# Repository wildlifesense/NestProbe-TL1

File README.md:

# NestProbe TL1

This repository has moved to [https://github.com/NikosVallianos/NestProbe/TL1](https://github.com/NikosVallianos/NestProbe/TL1)

I've used the TL1 reliably for over a year, but have also stared developing the TL2, which uses the Si7051 temperature sensor and the ATtiny816 MCU.
The NestProbe TL1 is a low cost, high accuracy, long-life temperature logger
developed at Wildlife Sense for sea turtle egg incubation research. This repository

Some aspects and decisions during development have been documented at [hackaday.io/project/27560-low-costpowersize-temperature-logger](https://hackaday.io/project/27560-low-costpowersize-temperature-logger).

The main components in the TL1 are:

| Component          | Model       |
|:-------------------|:------------|
| Microcontroller    | ATmega328PB |
| Temperature sensor | MAX30205    |
| EEPROM Memory      | AT25DN512C  |
| Crystal oscillator | ECS-.327-7-34B-C-TR (32.768kHz) |
| Battery type       | CR2032      |

Plus one SMD 0402 LED and a small number of pull-up resistors and decoupling capacitors.

The WSTL18 firmware and Eagle files are released under the GNU General Public
License version 3. This roughly means that you can use these files and designs,
manufacture the TL1 or derivatives and even sell them but you always have to
make the original source code or derivatives available under the same license.
See COPYING for details.

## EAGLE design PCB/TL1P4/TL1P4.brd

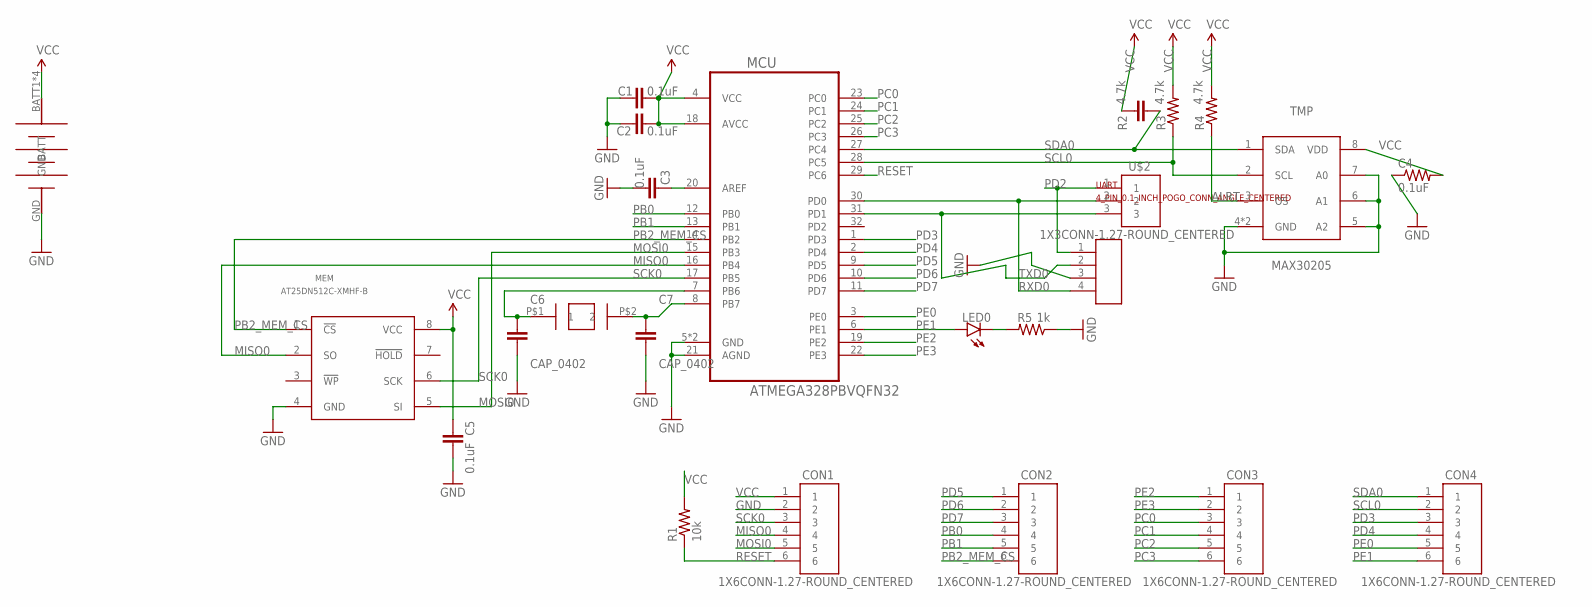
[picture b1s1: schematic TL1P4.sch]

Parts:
C1, C2, C3, C4, C5: 0.1uF; RES_CAP_0201
C6, C7: CAP_0402; SMD_0402
CON1, CON2, CON3, CON4: 1X6CONN-1.27-ROUND_CENTERED; 1X6_1.27_ROUND_CENTERED
LED0: LED_0402
MCU: ATMEGA328PBVQFN32; ATMEGA328PB_VFQFN32
MEM: AT25DN512C-XMHF-B; TSSSOP-8
R1: 10k; RES_CAP_0201
R2, R3, R4: 4.7k; RES_CAP_0201
R5: 1k; RES_CAP_0201
T1: ABS07AIG
TMP: MAX30205; MAX30205_TDFN8
U$1: LINX-CR2032-BAT-HLD-THM; CR2032-LINX-THM
U$2: 1X3CONN-1.27-ROUND_CENTERED; 1X3_1.27_ROUND_CENTERED
UART: 4_PIN_0.1_INCH_POGO_CONN_ANGLE_CENTERED; 4_PIN_0.1"_POGO_ANGLE_CENTERED

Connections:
ALRT: R4.2, TMP.3 (OS)
AREF: C3.1, MCU.20 (AREF)
GND: C1.2, C2.2, C3.2, C4.2, C5.2, C6.2, C7.2, CON1.2, MCU.5 (GND), MCU.21 (AGND), MCU.PAD (GND), MEM.4 (GND), R5.2, TMP.4 (GND), TMP.5 (A2), TMP.6 (A1), TMP.7 (A0), TMP.PAD (GND), U$1.GND, UART.3
MISO0: CON1.4, MCU.16 (PB4), MEM.2 (SO)
MOSI0: CON1.5, MCU.15 (PB3), MEM.5 (SI)
unnamed: C7.1, MCU.8 (PB7), T1.P$2 (2)
unnamed: C6.1, MCU.7 (PB6), T1.P$1 (1)
unnamed: LED0.CATHODE (C), R5.1
PB0: CON2.4, MCU.12 (PB0)
PB1: CON2.5, MCU.13 (PB1)
PB2_MEM_CS: CON2.6, MCU.14 (PB2), MEM.1 (!CS!)
PC0: CON3.3, MCU.23 (PC0)
PC1: CON3.4, MCU.24 (PC1)
PC2: CON3.5, MCU.25 (PC2)
PC3: CON3.6, MCU.26 (PC3)
PD2: U$2.1, UART.1
PD3: CON4.3, MCU.1 (PD3)
PD4: CON4.4, MCU.2 (PD4)
PD5: CON2.1, MCU.9 (PD5)
PD6: CON2.2, MCU.10 (PD6)
PD7: CON2.3, MCU.11 (PD7)
PE0: CON4.5, MCU.3 (PE0)
PE1: CON4.6, LED0.ANODE (A), MCU.6 (PE1)
PE2: CON3.1, MCU.19 (PE2)
PE3: CON3.2, MCU.22 (PE3)
RESET: CON1.6, MCU.29 (PC6), R1.2
RXD0: MCU.30 (PD0), U$2.2, UART.4
SCK0: CON1.3, MCU.17 (PB5), MEM.6 (SCK)
SCL0: CON4.2, MCU.28 (PC5), R3.2, TMP.2 (SCL)
SDA0: CON4.1, MCU.27 (PC4), R2.2, TMP.1 (SDA)
TXD0: MCU.31 (PD1), U$2.3, UART.2
VCC: C1.1, C2.1, C4.1, C5.1, CON1.1, MCU.4 (VCC), MCU.18 (AVCC), MEM.8 (VCC), R1.1, R2.1, R3.1, R4.1, TMP.8 (VDD), U$1.BATT1 (BATT), U$1.BATT2 (BATT), U$1.BATT3 (BATT), U$1.BATT4 (BATT)

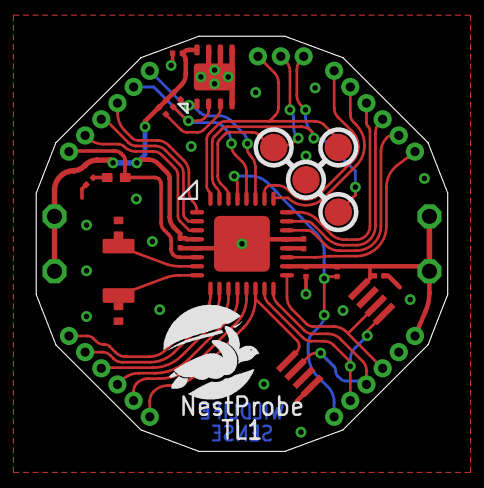
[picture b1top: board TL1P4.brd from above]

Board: 2 copper layers, 22.9 x 23.1 mm, 24 parts (1 on the bottom side), 32 nets.

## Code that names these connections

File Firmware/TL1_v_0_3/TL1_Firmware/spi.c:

/********************************************************************************

  spi.c: SPI module of NestProbe TL1 firmware.
 
  Copyright (C) 2017 Nikos Vallianos <nikos@wildlifesense.com>
  
  This file is part of NestProbe TL1 firmware.
  
  NestProbe TL1 firmware is free software: you can redistribute it and/or modify
  it under the terms of the GNU General Public License as published by
  the Free Software Foundation, either version 3 of the License, or
  any later version.
  
  NestProbe TL1 firmware is distributed in the hope that it will be useful,
  but WITHOUT ANY WARRANTY; without even the implied warranty of
  MERCHANTABILITY or FITNESS FOR A PARTICULAR PURPOSE.  See the
  GNU General Public License for more details.
  
  You should have received a copy of the GNU General Public License
  in the file COPYING along with this program.  If not,
  see <http://www.gnu.org/licenses/>.

  ********************************************************************************/
#include <avr/io.h>
#include <avr/interrupt.h>
#include "spi.h"

// #################### PORTS & PINS FOR SPI0. Don't change unless porting to another mcu ####################
//	MISO0 is PB4
//	SCK0 is PB5
//	MOSI0 is PB3
//	SS0 is PB2

// Initialize pins for spi communication
void spiEnable(void) {
	DDRB &= ~(1<<DDRB4);		// MISO is INPUT
	PORTB &= ~(1<<PORTB4);		// No pull (tri-state for inputs?)
	
	DDRB |= (1<<DDRB3);			// MOSI output
	PORTB &= ~(1<<PORTB3);		// Low

	DDRB |= (1<<DDRB5);			// SCK out
	PORTB &= ~(1<<PORTB5);		// Low

    PRR0 &= ~(1<<PRSPI0);								// Clock SPI0 clock, powers the module
	
	SPCR0 = (1<<SPE) | (1<<MSTR) | (0<<SPR1) | (0<<SPR0);		// Enable SPI, set to Master, set prescaler.
}

/*
 * spiDisable: Disable the SPI module and set it for lowest power consumption.
 * TODO: Add some fault detection: SPSR0.WCOL0
 */
void spiDisable(void) {
	SPCR0 = 0;											// Disable SPI.
	PRR0 |= (1<<PRSPI0);								// Cut off SPI0 clock, shuts the module	
	DDRB  &= ~(1<<DDRB3|1<<DDRB4|1<<DDRB5);				// MOSI0, SCK0, MISO0 pins are input
	PORTB |=  (1<<PORTB3|1<<PORTB4|1<<PORTB5);			// Pull-up enabled, reduces consumption.
}

// When a serial transfer is complete, the SPIF flag is set.
uint8_t spiTradeByte(uint8_t byte) {
	SPDR0 = byte;										
	loop_until_bit_is_set(SPSR0, SPIF);			
	return SPDR0;
}



// Shift an array out and retain returned data.
void spiExchangeArray(uint8_t * dataout, uint8_t * datain, uint8_t len) {
	for (uint8_t i = 0; i < len; i++) {
		datain[i] = spiTradeByte(dataout[i]);
	}
}



// Shift an array out and discard returned data.
void spiTransmitArray(uint8_t * dataout, uint8_t len) {
	for (uint8_t i = 0; i < len; i++) {
		spiTradeByte(dataout[i]);
	}
}

// Shift an array in while sending scrap data
void spiReceiveArray(uint8_t * datain, uint8_t len) {
	for (uint8_t i=0; i<len; i++) {
		datain[i] = spiTradeByte(0x00);
	}
}

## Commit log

2019-01-09 Added list of parts
2019-01-09 Removed few gerber files
2019-01-09 Removed some more gerber files
2019-01-09 Formatted prices and costs to currency.
2019-01-09 Removed two files
2019-01-10 Added README
2019-01-10 Updates on README
2019-01-10 Updates on CR2032
2019-01-11 Updates to README

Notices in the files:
parts and their libraries:
SparkFun-Aesthetics: Licensing: Creative Commons ShareAlike 4.0 International - https://creativecommons.org/licenses/by-sa/4.0
